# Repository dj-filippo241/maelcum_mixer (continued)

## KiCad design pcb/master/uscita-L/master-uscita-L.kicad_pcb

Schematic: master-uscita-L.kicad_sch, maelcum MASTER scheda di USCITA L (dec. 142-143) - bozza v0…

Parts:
C1, C2: 1000u 35V; CP_Radial_D12.5mm_P5.00mm
C3, C4: 100n 50V; C_0805_2012Metric
C5, C7: 10u 35V; CP_Radial_D5.0mm_P2.00mm
C6, C8: 47u 35V; CP_Radial_D6.3mm_P2.50mm
C9, C10, C11, C12, C13, C14, C16, C17, C19, C20, C22: 100n; C_0805_2012Metric
C15, C18: 15n C0G; C_1206_3216Metric
C21: 1u; C_1206_3216Metric
C23: 2u2 X7R; C_1206_3216Metric
D1, D3, D5, D6, D7, D8, D9, D10, D11, D12, D13, D14, D15, D16, D17, D18, D19, D20, D21, D22, D23, D24, D25, D26, D27, D28, D29, D30, D31, D32, D33, D34, D35, D36, D37, D38, D39, D40, D43: 1N4148W; D_SOD-123
D2, D4: S1G; D_SMA
D41, D42, D44: BAT54W; SOT-323_SC-70
FB1, FB2: ferrite 600R 2A; L_1206_3216Metric
H1, H2: CHASSIS; MountingHole_3.2mm_M3_Pad
J1: C96 maschio; DIN41612_C_3x32_Male_Horizontal_THT
J2: 2x7 cavo piatto; PinHeader_2x07_P2.54mm_Vertical
J3: 2x5 cavo; PinHeader_2x05_P2.54mm_Vertical
J4: 2x2 cavo; PinHeader_2x02_P2.54mm_Vertical
K1, K2, K3: G6K-2F DC5; Relay_DPDT_Omron_G6K-2F
Q1, Q3, Q8, Q10: BF245A; TO-92_Inline_Wide
Q2, Q6, Q9, Q13: MJE340; TO-126-3_Vertical
Q4, Q7, Q11, Q14: MJE350; TO-126-3_Vertical
Q5, Q12: BC847B; SOT-23
Q15: AO3400A; SOT-23
Q16: 2N7002; SOT-23
R1, R3: 120 1%; R_0805_2012Metric
R2, R4: 1k62 1%; R_0805_2012Metric
R5, R6, R32: 10k 0.1%; R_0805_2012Metric
R7, R8, R9, R10, R20, R21: 47; R_0805_2012Metric
R11, R22: 2k2 1%; R_0805_2012Metric
R12, R23: 1k 1%; R_0805_2012Metric
R13, R14, R24, R25: 33 1%; R_1206_3216Metric
R15, R17, R26, R27, R29: 1k 0.1%; R_0805_2012Metric
R16, R18, R28: 1M 1%; R_0805_2012Metric
R19, R30: 220k 1%; R_0805_2012Metric
R31: 100k 0.1%; R_0805_2012Metric
R33, R35: 118k 1%; R_0805_2012Metric
R34, R36, R37, R38: 10k 1%; R_0805_2012Metric
R39, R41: 4k7; R_0805_2012Metric
R40: 680k; R_0805_2012Metric
R42, R44, R48, R50: 10k; R_0805_2012Metric
R43: 100; R_0805_2012Metric
R45: 1k; R_0805_2012Metric
R46: 160k 1%; R_0805_2012Metric
R47: 21k5 1%; R_0805_2012Metric
R49: 1M2 1%; R_0805_2012Metric
U1, U2, U11, U21: OPA1612AIDR; SOIC-8_3.9x4.9mm_P1.27mm
U3, U4: LM339; SOIC-14_3.9x8.7mm_P1.27mm
U5: TL431; SOT-23
U12, U22: TL071; SOIC-8_3.9x4.9mm_P1.27mm
U40: LM317; TO-220-3_Vertical
U41: LM337; TO-220-3_Vertical

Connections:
+5V: C22.1, D43.1 (K), J1.a21, J1.a22, J4.1, J4.3, K1.1, K2.1, K3.1, R37.1, R40.1, R42.1, R44.2, R45.1, R48.2, R50.2, U4.3 (V+)
+18V: C6.1, C9.1, C11.1, C13.1, C16.1, C19.1, D1.1 (K), D2.2 (A), R1.1, U1.8 (V+), U2.8 (V+), U3.3 (V+), U12.7 (V+), U22.7 (V+), U40.2 (VO)
-18V: C8.2, C10.2, C12.2, C14.2, C17.2, C20.2, D3.2 (A), D4.1 (K), R3.1, U1.4 (V-), U2.4 (V-), U3.12 (V-), U12.4 (V-), U22.4 (V-), U41.3 (VO)
AC_OK: J1.c17, R44.1, U4.7 (+)
ADJ+: C5.1, D1.2 (A), R1.2, R2.1, U40.1 (ADJ)
ADJ-: C7.2, D3.1 (K), R3.2, R4.1, U41.1 (ADJ)
AGND: C1.2, C2.1, C3.2, C4.1, C5.2, C6.2, C7.1, C8.1, C9.2, C10.1, C11.2, C12.1, C13.2, C14.1, C16.2, C17.1, C19.2, C20.1, J1.a13, J1.a14, J1.a15, J1.a16, J1.a17, J1.a18, J1.a19, J1.a20, J2.1, J2.3, J2.5, J2.7, J2.9, J2.11, J3.1, J3.4, J3.7, J3.10, R2.2, R4.2, R18.2, R29.2, R32.2, R34.2, R36.2, U2.3 (+), U2.5 (+), U3.11 (+), U12.3 (+), U22.3 (+)
B2_C: Q12.2 (E), Q14.3 (B), R23.2
B2_H: Q5.2 (E), Q7.3 (B), R12.2
BC: R6.2, R8.1, U2.1
BH: R7.1, U1.6 (-), U1.7
BIN: R5.2, R6.1, U2.2 (-)
BOC: K2.6, R8.2
BOH: K2.3, R7.2
BOOTH_L: J2.6, R5.1, U1.5 (+)
BU_C: D23.2 (A), Q8.2 (S), Q9.3 (B), R20.2
BU_H: D5.2 (A), Q1.2 (S), Q2.3 (B), R9.2
CHALF: R37.2, R38.1, U3.9 (+)
CHASSIS: H1.1, H2.1, J1.a25, J1.a26
CLAT: C21.1, D41.3 (K), R39.2, R40.2, U3.8 (-)
CLD: R31.2, R32.1, U3.5 (+), U3.6 (-)
CLIP_L: D42.3 (K), J2.13, R41.2, R42.2
CLO: R41.1, U3.14
CLX: R39.1, U3.1, U3.2
CT: C23.1, D44.1 (A), R49.2, U4.9 (+)
CTN: R35.2, R36.1, U3.4 (-)
CTP: R33.2, R34.1, U3.7 (+), U3.10 (-)
CTRL_GND: C21.2, C22.2, C23.2, D41.1 (A), D42.1 (A), J1.a23, J1.a24, J1.c16, J1.c20, J1.c24, J1.c28, J4.2, J4.4, Q15.2 (S), Q16.2 (S), R38.2, R47.2, U4.11 (+), U4.12 (V-), U5.3 (A)
D22: R46.2, R47.1, U4.5 (+)
DRV_C: Q12.3 (C), Q13.3 (B), R22.1, U21.1
DRV_H: Q5.3 (C), Q6.3 (B), R11.1, U11.1
E1_C: Q13.1 (E), R24.1
E1_H: Q6.1 (E), R13.1
E2_C: Q14.1 (E), R25.1
E2_H: Q7.1 (E), R14.1
GLOBAL_MUTE: J1.c9, Q16.3 (D)
INN_C: R26.2, R27.2, U21.2 (-)
INN_H: R17.2, R18.1, U11.2 (-)
INP_C: R28.2, R29.1, U21.3 (+)
INP_H: R15.2, R16.2, U11.3 (+)
J1S_C: Q8.1 (G), R20.1
J1S_H: Q1.1 (G), R9.1
J2S_C: Q10.1 (G), R21.1
J2S_H: Q3.1 (G), R10.1
KD: D43.2 (A), K1.8, K2.8, K3.8, Q15.3 (D)
KG: Q15.1 (G), R43.2
KG0: Q16.1 (G), R43.1, R50.1, U4.14
MAST_L: J2.2, U1.3 (+)
MID_C: Q12.1 (B), R22.2, R23.1
MID_H: Q5.1 (B), R11.2, R12.1
MRX: R15.1, R26.1, U1.1, U1.2 (-)
NB2_C: D40.1 (K), Q10.3 (D), Q11.3 (B)
NB2_H: D22.1 (K), Q3.3 (D), Q4.3 (B)
NU: U2.6 (-), U2.7
OUT_C: D31.1 (K), D32.2 (A), K1.6, R24.2, R25.2, R27.1, R30.1, U21.5 (+)
OUT_H: D13.1 (K), D14.2 (A), K1.3, R13.2, R14.2, R17.1, R19.1, R31.1, U11.5 (+)
RAW+22: J1.a5, J1.a6, R46.1
RAW+26: FB1.1, J1.a9, J1.a10
RAW-26: FB2.1, J1.a11, J1.a12
REC_L: J2.10, K3.3
REC_R: J2.12, K3.6
ROK: D44.3 (K), R48.1, R49.1, U4.1, U4.2
S1_C: D23.1 (K), D24.2 (A)
S1_H: D5.1 (K), D6.2 (A)
S2_C: D24.1 (K), D25.2 (A)
S2_H: D6.1 (K), D7.2 (A)
S3_C: D25.1 (K), D26.2 (A)
S3_H: D7.1 (K), D8.2 (A)
S4_C: D26.1 (K), D27.2 (A)
S4_H: D8.1 (K), D9.2 (A)
S5_C: D27.1 (K), D28.2 (A)
S5_H: D9.1 (K), D10.2 (A)
S6_C: D28.1 (K), D29.2 (A)
S6_H: D10.1 (K), D11.2 (A)
S7_C: D29.1 (K), D30.2 (A)
S7_H: D11.1 (K), D12.2 (A)
S8_C: D30.1 (K), D31.2 (A)
S8_H: D12.1 (K), D13.2 (A)
SVN_C: C18.1, R30.2, U22.2 (-)
SVN_H: C15.1, R19.2, U12.2 (-)
SV_C: C18.2, R28.1, U22.6
SV_H: C15.2, R16.1, U12.6
T1_C: D32.1 (K), D33.2 (A)
T1_H: D14.1 (K), D15.2 (A)
T2_C: D33.1 (K), D34.2 (A)
T2_H: D15.1 (K), D16.2 (A)
T3_C: D34.1 (K), D35.2 (A)
T3_H: D16.1 (K), D17.2 (A)
T4_C: D35.1 (K), D36.2 (A)
T4_H: D17.1 (K), D18.2 (A)
T5_C: D36.1 (K), D37.2 (A)
T5_H: D18.1 (K), D19.2 (A)
T6_C: D37.1 (K), D38.2 (A)
T6_H: D19.1 (K), D20.2 (A)
T7_C: D38.1 (K), D39.2 (A)
T7_H: D20.1 (K), D21.2 (A)
T8_C: D39.1 (K), D40.2 (A)
T8_H: D21.1 (K), D22.2 (A)
UB_C: U21.6 (-), U21.7
UB_H: U11.6 (-), U11.7
V26F+: C1.1, C3.1, D2.1 (K), FB1.2, Q1.3 (D), Q2.2 (C), Q6.2 (C), Q8.3 (D), Q9.2 (C), Q13.2 (C), R33.1, U40.3 (VI)
V26F-: C2.2, C4.2, D4.2 (A), FB2.2, Q3.2 (S), Q4.2 (C), Q7.2 (C), Q10.2 (S), Q11.2 (C), Q14.2 (C), R10.2, R21.2, R35.1, U41.2 (VI)
VM_C: Q11.1 (E), U21.4 (V-)
VM_H: Q4.1 (E), U11.4 (V-)
VP_C: Q9.1 (E), U21.8 (V+)
VP_H: Q2.1 (E), U11.8 (V+)
VREF: R45.2, U4.4 (-), U4.6 (-), U4.8 (-), U4.10 (-), U5.1 (K), U5.2 (REF)
XBC: J3.6, K2.5
XBH: J3.5, K2.4
XMC: J3.3, K1.5
XMH: J3.2, K1.4
XRL: J3.8, K3.4
XRR: J3.9, K3.5

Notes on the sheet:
BACKPLANE C96 (classe MASTER-OUT, dec. 143): solo alimentazioni
ALIMENTAZIONE [M]: statici +-26 filtrati, +-18 locali (LM317/337)
RICEVITORE del MASTER e DRIVER del BOOTH [B3] (OPA1612 diretto, §3.4)
STADIO D'USCITA caldo [F]+[G] (bootstrap, dec. 86)
STADIO D'USCITA freddo [F]+[G] (bootstrap, invertente)
CLIP detector: finestra sul caldo, soglia 0,86 x statico, tenuta ~0,5 s (NOTA, da simulare)
RELE' di MASTER e BOOTH (G6K-2F, 5 V, 237 ohm; eccitati = suono, failsafe)
MUTE CONTROLLER [L] (mute-ctrl.cir, RISULTATI-mute-ctrl.md)
CONNETTORI: J2 dalla scheda di segnale, J3 verso la schedina dei connettori sul retro

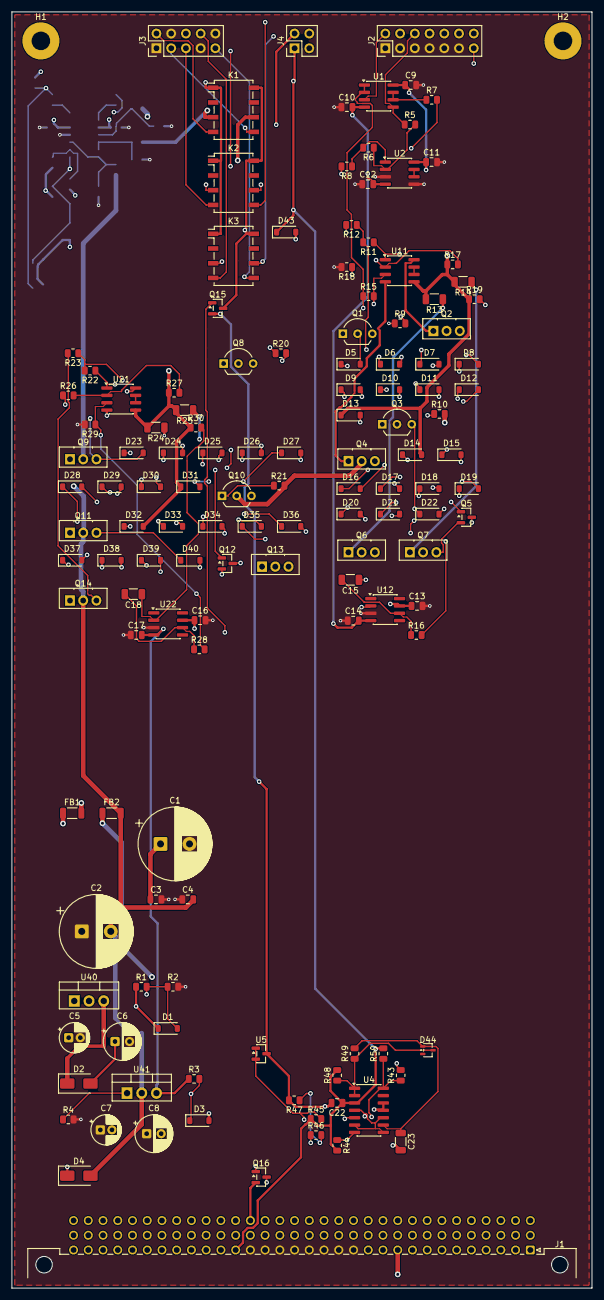
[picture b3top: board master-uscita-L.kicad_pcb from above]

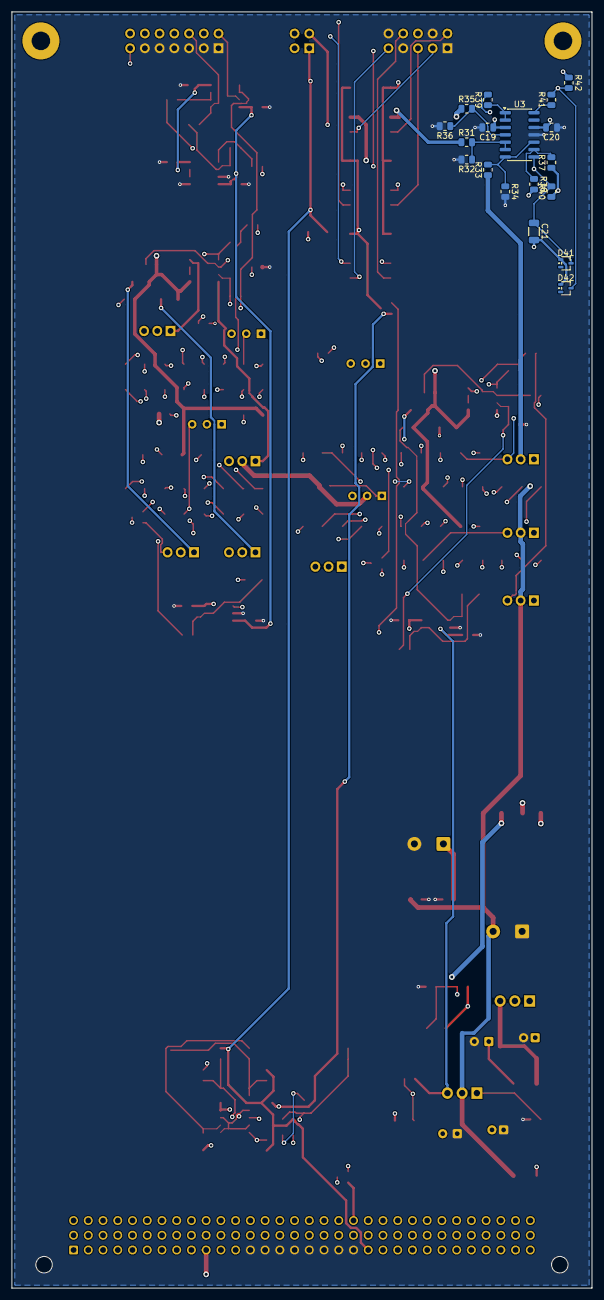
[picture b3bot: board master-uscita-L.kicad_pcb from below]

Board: 4 copper layers, 100.0 x 220.0 mm, 155 parts (18 on the bottom side), 113 nets.

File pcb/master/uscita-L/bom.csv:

quantita;valore;impronta;riferimenti;nota
1;1000u 35V;CP_Radial_D12.5mm_P5.00mm;C1;bulk locale [M] (master-out §3.8)
2;15n C0G;C_1206_3216Metric;C15 C18;fc 0,048 Hz (Test 12)
1;1000u 35V;CP_Radial_D12.5mm_P5.00mm;C2;
1;1u;C_1206_3216Metric;C21;
1;2u2 X7R;C_1206_3216Metric;C23;CT +-10 %
2;100n 50V;C_0805_2012Metric;C3 C4;
2;10u 35V;CP_Radial_D5.0mm_P2.00mm;C5 C7;
2;47u 35V;CP_Radial_D6.3mm_P2.50mm;C6 C8;
11;100n;C_0805_2012Metric;C9 C10 C11 C12 C13 C14 C16 C17 C19 C20 C22;
1;1N4148W;D_SOD-123;D1;scarica Cadj
1;S1G;D_SMA;D2;protezione inversa
37;1N4148W;D_SOD-123;D3 D5 D6 D7 D8 D9 D10 D11 D12 D13 D14 D15 D16 D17 D18 D19 D20 D21 D22 D23 D24 D25 D26 D27 D28 D29 D30 D31 D32 D33 D34 D35 D36 D37 D38 D39 D40;
1;S1G;D_SMA;D4;
2;BAT54W;SOT-323_SC-70;D41 D42;
1;1N4148W;D_SOD-123;D43;scarica delle bobine: 1,0 ms (RISULTATI-mute-ctrl)
1;BAT54W;SOT-323_SC-70;D44;scarica CT: riarmo >= 1,5 s
2;ferrite 600R 2A;L_1206_3216Metric;FB1 FB2;
1;C96 maschio;DIN41612_C_3x32_Male_Horizontal_THT;J1;DIN 41612 C 3x32; classe MASTER-OUT (dec. 143): RAW+-26, +5V, CTRL_GND, c9, c17, RAW+22
1;2x7 cavo piatto;PinHeader_2x07_P2.54mm_Vertical;J2;cavo piatto dalla scheda di segnale (stessa piedinatura del suo J2)
1;2x5 cavo;PinHeader_2x05_P2.54mm_Vertical;J3;NOTA: verso la schedina XLR/TRS sul retro (dec. 141)
1;2x2 cavo;PinHeader_2x02_P2.54mm_Vertical;J4;NOTA: +5V e CTRL_GND verso la scheda comandi (LED, LM3915): non passano dalla scheda di segnale
1;G6K-2F DC5;Relay_DPDT_Omron_G6K-2F;K1;MASTER L caldo e freddo
1;G6K-2F DC5;Relay_DPDT_Omron_G6K-2F;K2;BOOTH L caldo e freddo
1;G6K-2F DC5;Relay_DPDT_Omron_G6K-2F;K3;REC L e R [C3]
2;BF245A;TO-92_Inline_Wide;Q1 Q8;CCS ~4 mA (NJF245 in sim; Idss da selezionare)
1;AO3400A;SOT-23;Q15;driver dei relè, logic level
1;2N7002;SOT-23;Q16;c9: basso = suona, alto (pull-up nei moduli) = muto
2;MJE340;TO-126-3_Vertical;Q2 Q9;pass del rail +: 0,75 W a riposo, rame >= 4 cm2 (v0.3 punto 1); pinout da verificare
2;BF245A;TO-92_Inline_Wide;Q3 Q10;CCS ~4 mA
2;MJE350;TO-126-3_Vertical;Q4 Q11;pass del rail -: 0,75 W a riposo, rame >= 4 cm2; pinout da verificare
2;BC847B;SOT-23;Q5 Q12;moltiplicatore di Vbe (QMULT in sim): vicino a Q1/Q2 per l'inseguimento termico
2;MJE340;TO-126-3_Vertical;Q6 Q13;finale +; corto: 106 mA auto-limitati, 1,0 W medi
2;MJE350;TO-126-3_Vertical;Q7 Q14;finale -
2;120 1%;R_0805_2012Metric;R1 R3;
2;2k2 1%;R_0805_2012Metric;R11 R22;
2;1k 1%;R_0805_2012Metric;R12 R23;
4;33 1%;R_1206_3216Metric;R13 R14 R24 R25;
1;1k 0.1%;R_0805_2012Metric;R15;Rsrc: con Rinj 1M attenua 0,999, Rf/Rg guadagna 1,001
1;1M 1%;R_0805_2012Metric;R16;iniezione del servo
3;1k 0.1%;R_0805_2012Metric;R17 R27 R29;
1;1M 1%;R_0805_2012Metric;R18;
2;220k 1%;R_0805_2012Metric;R19 R30;
1;1k62 1%;R_0805_2012Metric;R2;18,1 V
1;1k 0.1%;R_0805_2012Metric;R26;freddo invertente: resistenze appaiate 0,1 % (CMRR ~60 dB)
1;1M 1%;R_0805_2012Metric;R28;NOTA: servo sul piedino + con partitore 1M/1k (cella dei servo)
1;100k 0.1%;R_0805_2012Metric;R31;
2;118k 1%;R_0805_2012Metric;R33 R35;
4;10k 1%;R_0805_2012Metric;R34 R36 R37 R38;
2;4k7;R_0805_2012Metric;R39 R41;
1;1k62 1%;R_0805_2012Metric;R4;
1;680k;R_0805_2012Metric;R40;tenuta: 680k x 1u, soglia a meta' = 0,47 s
1;10k;R_0805_2012Metric;R42;NOTA: CLIP alto = LED acceso (clip)
1;100;R_0805_2012Metric;R43;
1;10k;R_0805_2012Metric;R44;pull-up di AC_OK (open collector dal box)
1;1k;R_0805_2012Metric;R45;
1;160k 1%;R_0805_2012Metric;R46;finestra del +22: < 21,2 V = muto
1;21k5 1%;R_0805_2012Metric;R47;
1;10k;R_0805_2012Metric;R48;
1;1M2 1%;R_0805_2012Metric;R49;RT: accensione 1,61-1,97 s
3;10k 0.1%;R_0805_2012Metric;R5 R6 R32;
1;10k;R_0805_2012Metric;R50;OKD: alto = suona
1;47;R_0805_2012Metric;R7;NOTA: 47 ohm di uscita prima del relè
5;47;R_0805_2012Metric;R8 R9 R10 R20 R21;
1;OPA1612AIDR;SOIC-8_3.9x4.9mm_P1.27mm;U1;NOTA: ricevitore del cavo J2 (il caldo e il freddo caricano 500 ohm); caldo del booth
1;OPA1612AIDR;SOIC-8_3.9x4.9mm_P1.27mm;U11;composito H: rail a bootstrap (dec. 86); niente 100n rail-OUT (v0.3c)
2;TL071;SOIC-8_3.9x4.9mm_P1.27mm;U12 U22;servo DC su +-18 statici (FET, Iq bassa: non pesa sul bootstrap)
1;OPA1612AIDR;SOIC-8_3.9x4.9mm_P1.27mm;U2;freddo del booth; sezione B libera a massa
1;OPA1612AIDR;SOIC-8_3.9x4.9mm_P1.27mm;U21;composito C: rail a bootstrap (dec. 86); niente 100n rail-OUT (v0.3c)
1;LM339;SOIC-14_3.9x8.7mm_P1.27mm;U3;NOTA: clip detector (correzione 20 della review)
1;LM339;SOIC-14_3.9x8.7mm_P1.27mm;U4;supervisore e timer
1;LM317;TO-220-3_Vertical;U40;NOTA: +-18 locali, ~30 mA
1;LM337;TO-220-3_Vertical;U41;
1;TL431;SOT-23;U5;2,495 V

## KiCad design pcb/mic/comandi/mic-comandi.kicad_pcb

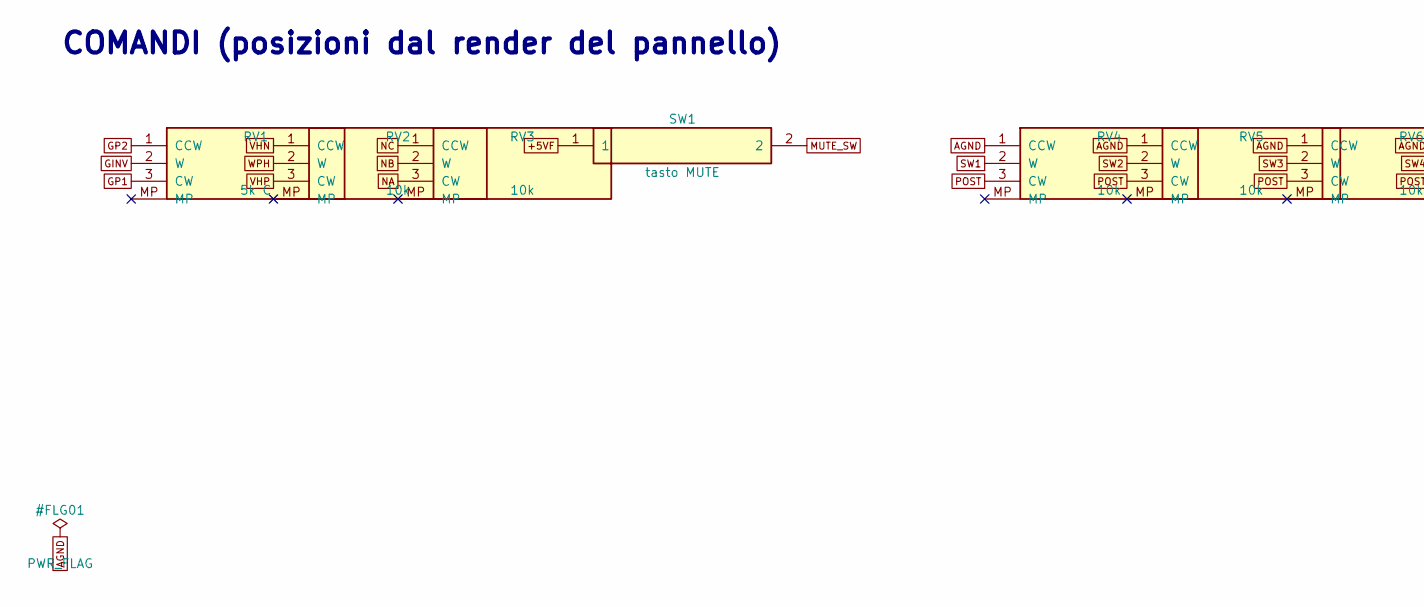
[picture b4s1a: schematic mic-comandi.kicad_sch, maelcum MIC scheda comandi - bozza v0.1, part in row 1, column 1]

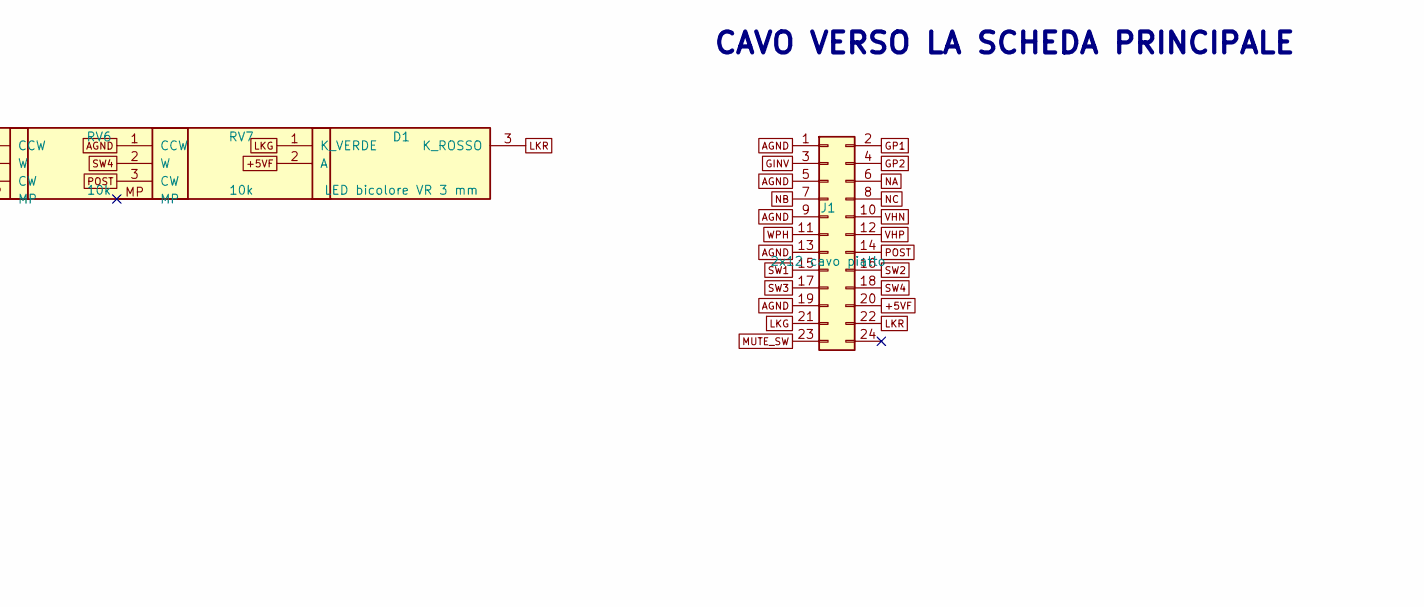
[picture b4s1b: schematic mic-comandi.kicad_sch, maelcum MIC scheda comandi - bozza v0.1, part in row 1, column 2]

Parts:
D1: LED bicolore VR 3 mm; LED_D3.0mm-3
J1: 2x12 cavo piatto; PinHeader_2x12_P2.54mm_Vertical
RV1: 5k C; Potentiometer_Alps_RK09L_Single_Vertical
RV2, RV3, RV4, RV5, RV6, RV7: 10k; Potentiometer_Alps_RK09L_Single_Vertical
SW1: tasto MUTE; SW_PUSH_6mm

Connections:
+5VF: D1.2 (A), J1.20, SW1.1
AGND: J1.1, J1.5, J1.9, J1.13, J1.19, RV4.1 (CCW), RV5.1 (CCW), RV6.1 (CCW), RV7.1 (CCW)
GINV: J1.3, RV1.2 (W)
GP1: J1.2, RV1.3 (CW)
GP2: J1.4, RV1.1 (CCW)
LKG: D1.1 (K_VERDE), J1.21
LKR: D1.3 (K_ROSSO), J1.22
MUTE_SW: J1.23, SW1.2
NA: J1.6, RV3.3 (CW)
NB: J1.7, RV3.2 (W)
NC: J1.8, RV3.1 (CCW)
POST: J1.14, RV4.3 (CW), RV5.3 (CW), RV6.3 (CW), RV7.3 (CW)
SW1: J1.15, RV4.2 (W)
SW2: J1.16, RV5.2 (W)
SW3: J1.17, RV6.2 (W)
SW4: J1.18, RV7.2 (W)
VHN: J1.10, RV2.1 (CCW)
VHP: J1.12, RV2.3 (CW)
WPH: J1.11, RV2.2 (W)

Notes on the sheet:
COMANDI (posizioni dal render del pannello)
CAVO VERSO LA SCHEDA PRINCIPALE

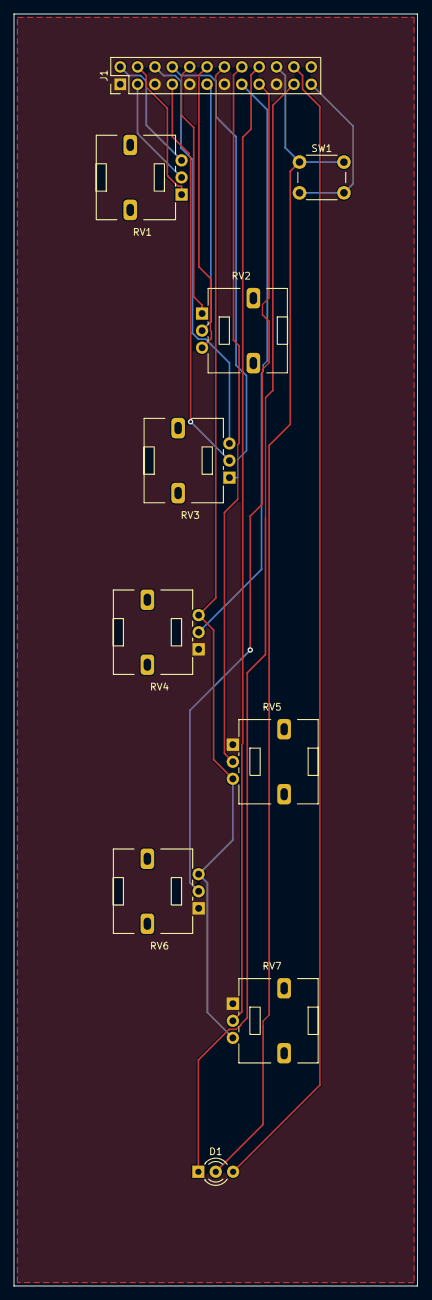
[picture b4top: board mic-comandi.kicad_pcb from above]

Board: 4 copper layers, 59.0 x 186.0 mm, 10 parts (0 on the bottom side), 19 nets.

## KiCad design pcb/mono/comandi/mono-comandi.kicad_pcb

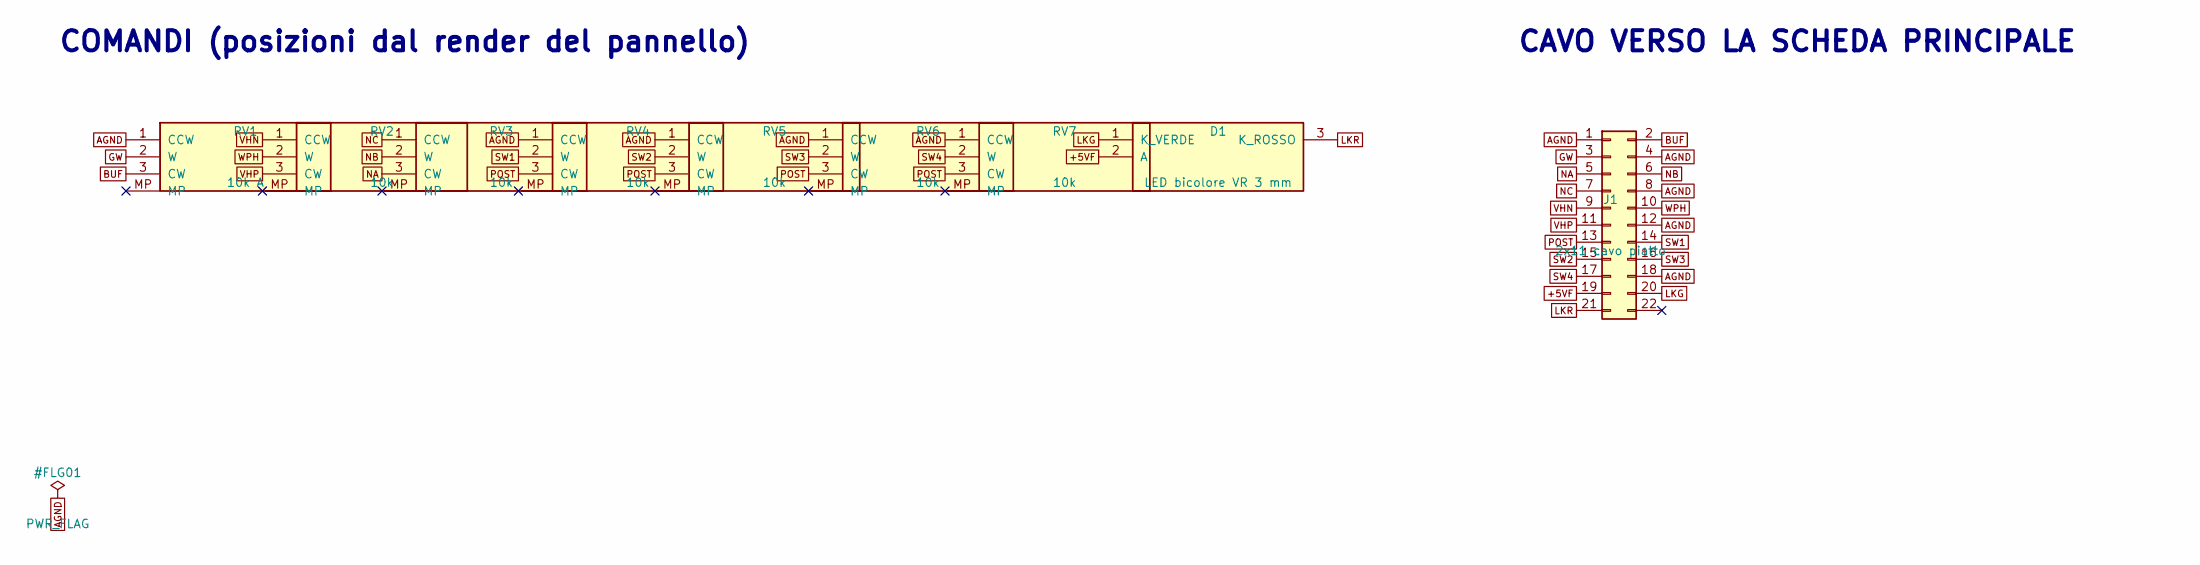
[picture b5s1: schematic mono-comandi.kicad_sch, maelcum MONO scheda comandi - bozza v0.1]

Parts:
D1: LED bicolore VR 3 mm; LED_D3.0mm-3
J1: 2x11 cavo piatto; PinHeader_2x11_P2.54mm_Vertical
RV1: 10k A; Potentiometer_Alps_RK09L_Single_Vertical
RV2, RV3, RV4, RV5, RV6, RV7: 10k; Potentiometer_Alps_RK09L_Single_Vertical

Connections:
+5VF: D1.2 (A), J1.19
AGND: J1.1, J1.4, J1.8, J1.12, J1.18, RV1.1 (CCW), RV4.1 (CCW), RV5.1 (CCW), RV6.1 (CCW), RV7.1 (CCW)
BUF: J1.2, RV1.3 (CW)
GW: J1.3, RV1.2 (W)
LKG: D1.1 (K_VERDE), J1.20
LKR: D1.3 (K_ROSSO), J1.21
NA: J1.5, RV3.3 (CW)
NB: J1.6, RV3.2 (W)
NC: J1.7, RV3.1 (CCW)
POST: J1.13, RV4.3 (CW), RV5.3 (CW), RV6.3 (CW), RV7.3 (CW)
SW1: J1.14, RV4.2 (W)
SW2: J1.15, RV5.2 (W)
SW3: J1.16, RV6.2 (W)
SW4: J1.17, RV7.2 (W)
VHN: J1.9, RV2.1 (CCW)
VHP: J1.11, RV2.3 (CW)
WPH: J1.10, RV2.2 (W)

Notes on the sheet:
COMANDI (posizioni dal render del pannello)
CAVO VERSO LA SCHEDA PRINCIPALE

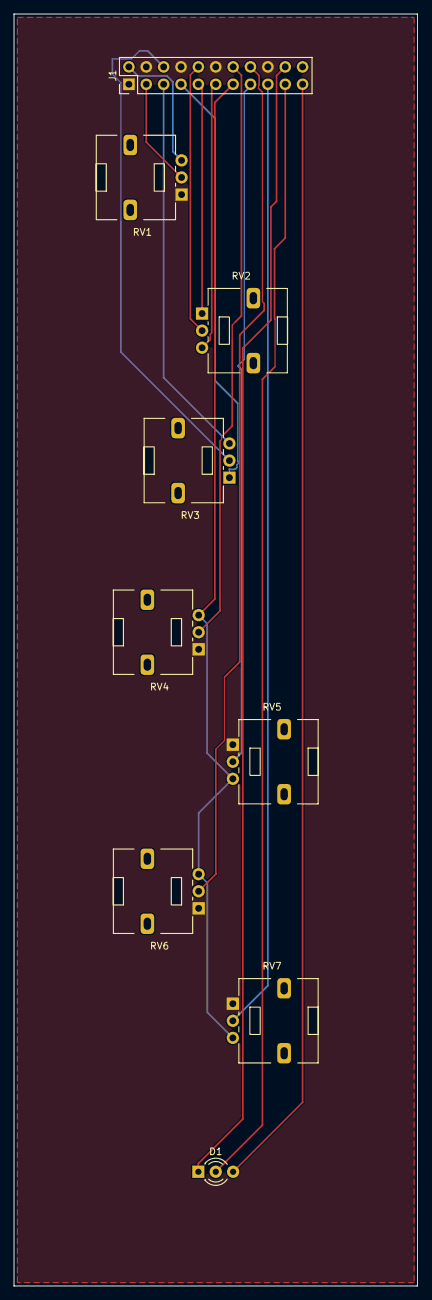
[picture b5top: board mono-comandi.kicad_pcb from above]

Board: 4 copper layers, 59.0 x 186.0 mm, 9 parts (0 on the bottom side), 17 nets.
